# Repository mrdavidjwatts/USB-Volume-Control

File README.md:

#USB-Volume-Control

Control Volume in your computer using this board! It takes advantage of the NicoHood HID library and core, make sure you have it installed in your Arduino IDE before running the code supplied - https://github.com/NicoHood/HID/wiki

##BOM

###Microcontroller

* Atmega32u4-AU

###Resistors:

* 2x 22 Ω 0805
* 300Ω 0805
* 10KΩ 0805

###Capacitors

* 0,1uF 0805
* 1uF 0805
* 10uF 0805
* 100uF 0805
* 22pF THT

###LEDs

* 2 x LED 1206 SMD
* LED THT 5mm

###Other

* USB Mini type B
* Rotary Encoder
* Crystal HC49S 16MHz
* 1x06 Header 2.54 mm or 0.1 in pitch

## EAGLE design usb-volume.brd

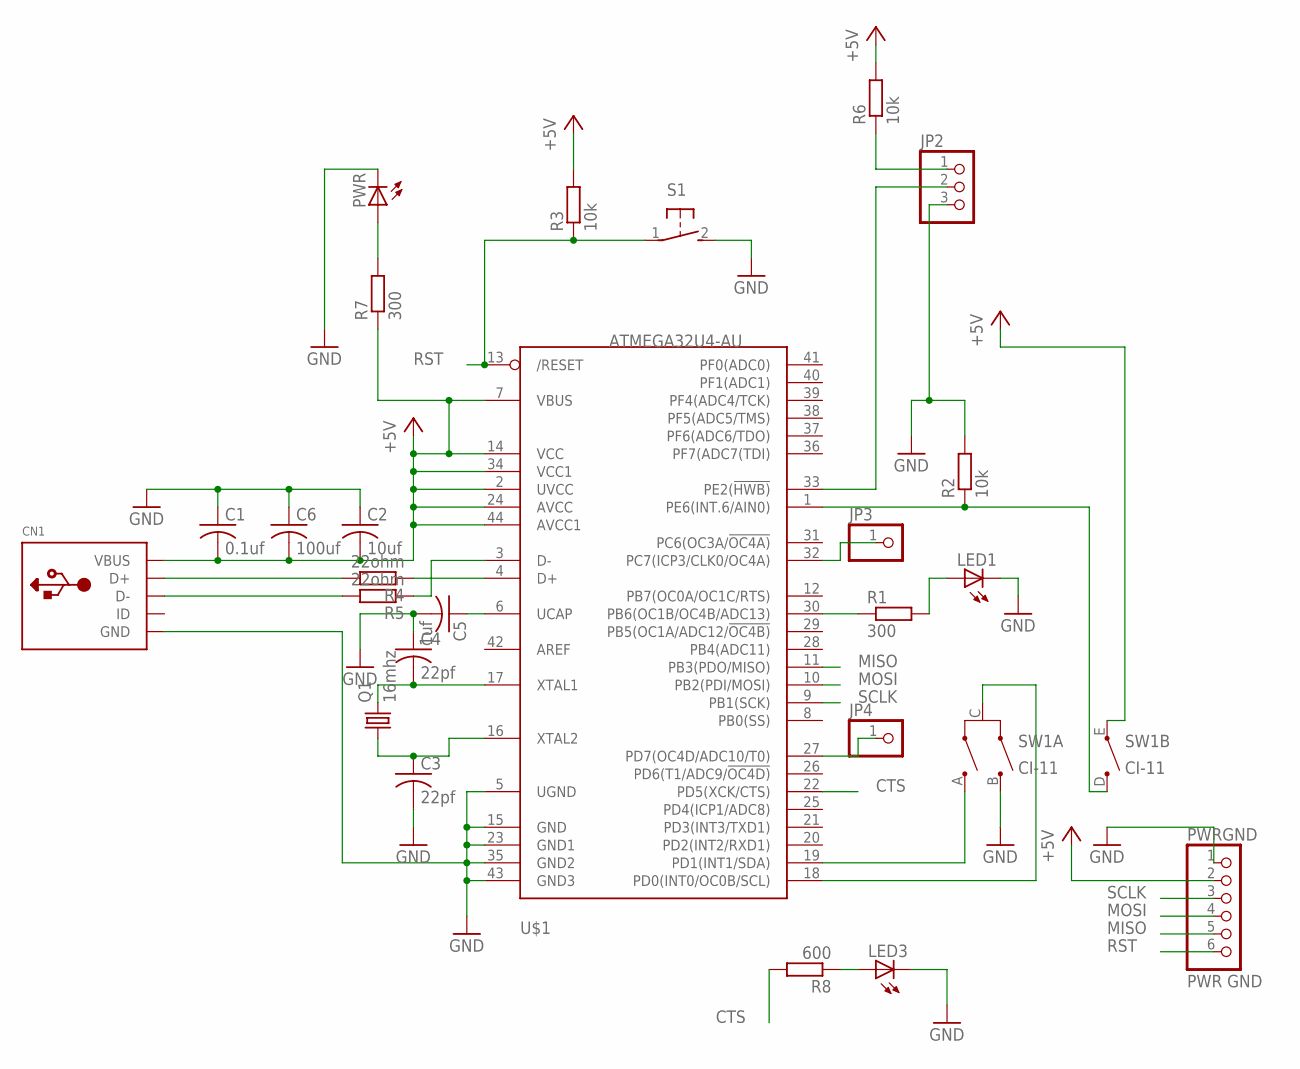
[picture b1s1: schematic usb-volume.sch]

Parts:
C1: 0.1uf; C0805
C2: 10uf; C0805
C3, C4: 22pf; C025-025X050
C5: 1uf; C0805
C6: 100uf; C0805
CN1: USBMINIB; USB-MINIB
JP2: PINHD-1X3; 1X03
JP3, JP4: PINHD-1X1; 1X01
LED1: LED5MM
LED3: LEDCHIPLED_1206; CHIPLED_1206
PWR: LEDCHIPLED_1206; CHIPLED_1206
PWRGND: PWR GND; 1X06
Q1: 16mhz; HC49/S
R1, R7: 300; R0805
R2, R3, R6: 10k; R0805
R4, R5: 22ohm; R0805
R8: 600; R0805
S1: 31-XX; B3F-31XX
SW1: CI-11
U$1: ATMEGA32U4-AU; TQFP44

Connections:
+5V: C1.2, C2.2, C6.2, CN1.VBUS, PWRGND.2, R3.2, R6.2, R7.1, SW1.E, U$1.2 (UVCC), U$1.7 (VBUS), U$1.14 (VCC), U$1.24 (AVCC), U$1.34 (VCC1), U$1.44 (AVCC1)
CTS: R8.2, U$1.22 (PD5(XCK/CTS))
GND: C1.1, C2.1, C3.2, C4.1, C5.2, C6.1, CN1.GND, JP2.3, LED1.K (C), LED3.C, PWR.C, PWRGND.1, R2.2, S1.2 (S), SW1.B, U$1.5 (UGND), U$1.15 (GND), U$1.23 (GND1), U$1.35 (GND2), U$1.43 (GND3)
MISO: PWRGND.5, U$1.11 (PB3(PDO/MISO))
MOSI: PWRGND.4, U$1.10 (PB2(PDI/MOSI))
unnamed: SW1.C, U$1.18 (PD0(INT0/OC0B/SCL))
unnamed: SW1.A, U$1.19 (PD1(INT1/SDA))
unnamed: C4.2, Q1.2, U$1.17 (XTAL1)
unnamed: R2.1, SW1.D, U$1.1 (PE6(INT.6/AIN0))
unnamed: C3.1, Q1.1, U$1.16 (XTAL2)
unnamed: CN1.D+, R4.2
unnamed: R5.1, U$1.3 (D-)
unnamed: R1.1, U$1.30 (PB6(OC1B/OC4B/ADC13))
unnamed: LED1.A, R1.2
unnamed: CN1.D-, R5.2
unnamed: R4.1, U$1.4 (D+)
unnamed: JP2.2, U$1.33 (PE2(!HWB))
unnamed: C5.1, U$1.6 (UCAP)
unnamed: JP2.1, R6.1
unnamed: PWR.A, R7.2
unnamed: JP3.1, U$1.32 (PC7(ICP3/CLK0/OC4A))
unnamed: LED3.A, R8.1
unnamed: JP4.1, U$1.27 (PD7(OC4D/ADC10/T0))
RST: PWRGND.6, R3.1, S1.1, U$1.13 (/RESET)
SCLK: PWRGND.3, U$1.9 (PB1(SCK))

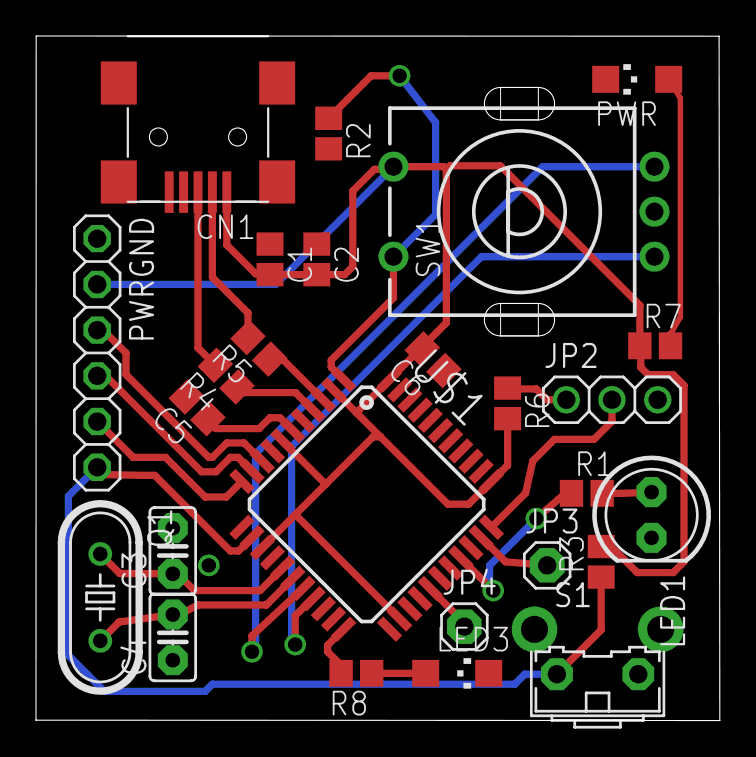
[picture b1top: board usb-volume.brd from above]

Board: 2 copper layers, 38.0 x 38.0 mm, 26 parts (0 on the bottom side), 25 nets.

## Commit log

2015-08-22 :tada: Added .gitattributes & .gitignore files
2015-08-22 USB Volume Control with an ATMEGA32U4
    This is a USB HID volume control for PCs and Macs
2015-08-22 updated schematics with values
2015-09-08 Added BOM
2015-09-09 Added long/short click support, debug info and minor changes
